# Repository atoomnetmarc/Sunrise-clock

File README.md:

# Status

**Experimental. Do not replicate.**

# Sunrise clock-hardware

Schematic and PCB files of the Sunrise clock. This sunrise clock tries to gently wake the user from its sleep using digital leds (SK6812) to simulate a sunrise and simultaneously playing soothing sounds through its crappy speaker using a I2S mono amplifier.\
1 display was not enough to view the time when the user has trouble dealing with dry eye syndrome so there are 3 displays capable of displaying a few characters each with a large font. Also, no touch screen so the user is able to change settings without looking using large-ish tactile buttons.

How the sunrise clock could look like:

My [Kicad library](https://github.com/atoomnetmarc/ATOOMNETKICAD) is used in this project.

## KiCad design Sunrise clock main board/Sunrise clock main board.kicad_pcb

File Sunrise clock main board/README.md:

# Status

**Experimental. Do not replicate.**

# Checklist V1.0 PCB

Worky (after workaround)?

:ballot_box_with_check: SD card auto disconnect when programming via USB\
:ballot_box_with_check: SD card, 1-bit SDIO\
:ballot_box_with_check: SD card, HSPI\
:ballot_box_with_check: RTC battery voltage follower opamp\
:ballot_box_with_check: 3.3V I2C\
:ballot_box_with_check: 5V I2C\
:ballot_box_with_check: INA219 current/power measuring\
:ballot_box_with_check: AT24C512C EEPROM\
:ballot_box_with_check: DS3231MZ mems RTC\
:ballot_box_with_check: BME280 sensor\
:ballot_box_with_check: MCP23017 I/O expander\
:ballot_box_with_check: LDR\
:ballot_box_with_check: LCD displays\
:ballot_box_with_check: Neopixel\
:ballot_box_with_check: Polyfuse F1\
:ballot_box_with_check: GPO2\
:ballot_box_with_check: I2S audio amplifier left channel (mono)\
:black_square_button: I2S audio amplifier right channel

# Errata

## V1.1

- Not build yet.

## V1.0

- VREF2 of U6 is incorrectly connected to +5V. It should be connected to EN. Workaround by disconnecting trace to VREF2 (pin7) and then connect EN (pin8) and VREF2 together.
- BME280 module A5 is a 5V one. Changed it for a 3.3V one. Workaround by disconnecting VCC from 5V and connect it to 3V.
- VIH of U8 74AHC125D on 5V too low for ESP32 output. Workaround by changing U8 from 74AHC125D to 74AHCT125D.
- INTA output voltage of MCP23017 exceeding input voltage of ESP32. Workaround by adding a 4K7/10K resistor divider.
- When powering the ESP32 by USB, the entire boards gets powered including the LED-strip which can potentially pull more than USB can provide. Workaround by moving D1 from parallel to ground and 5V to in series of 5V.
- External IO current measuring does not work with loads under 200mA and not great above that. Workaround by fitting a INA219 module between the 5V input of J1 and the rest of the board.

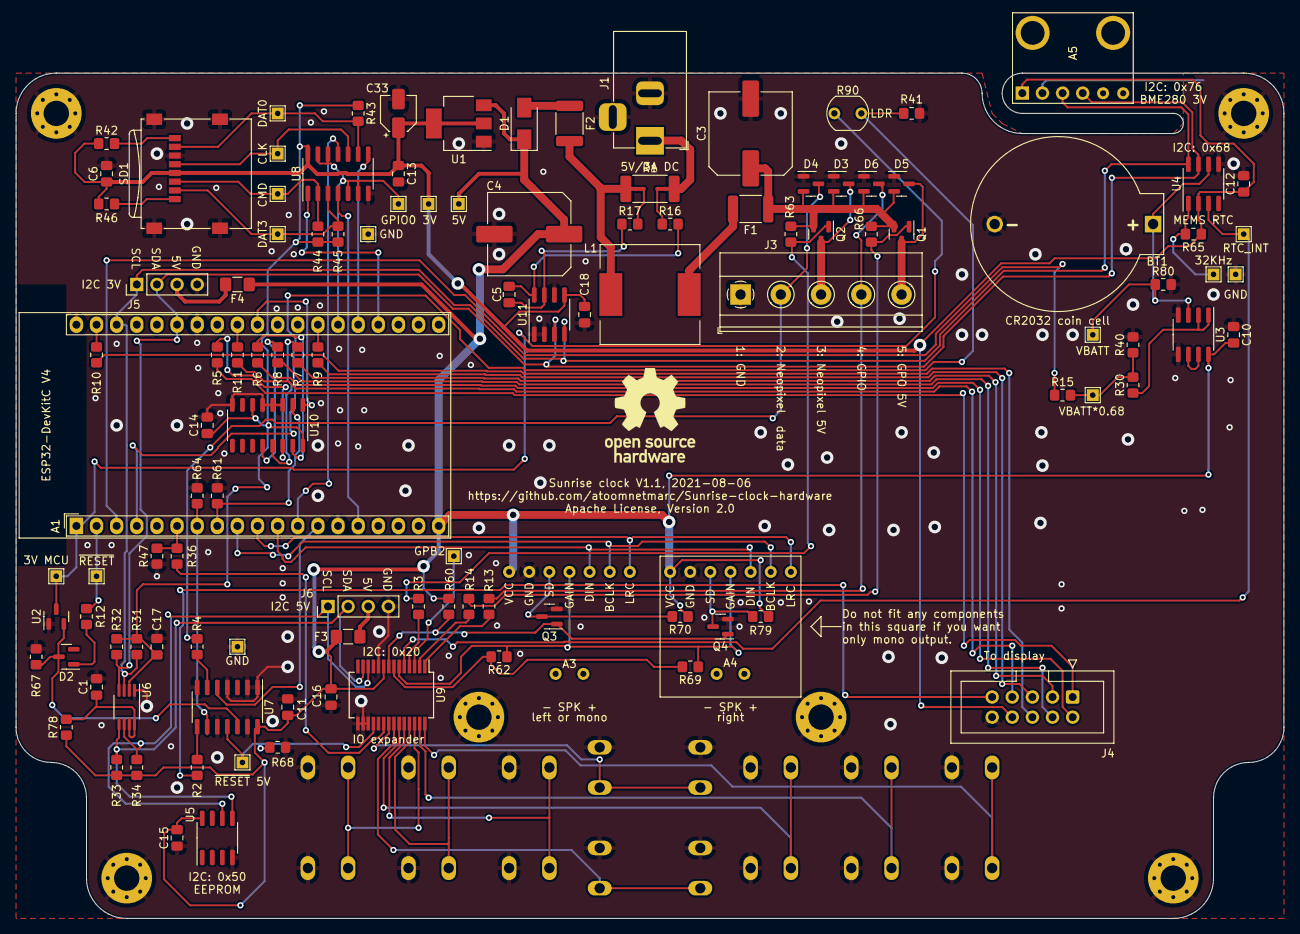
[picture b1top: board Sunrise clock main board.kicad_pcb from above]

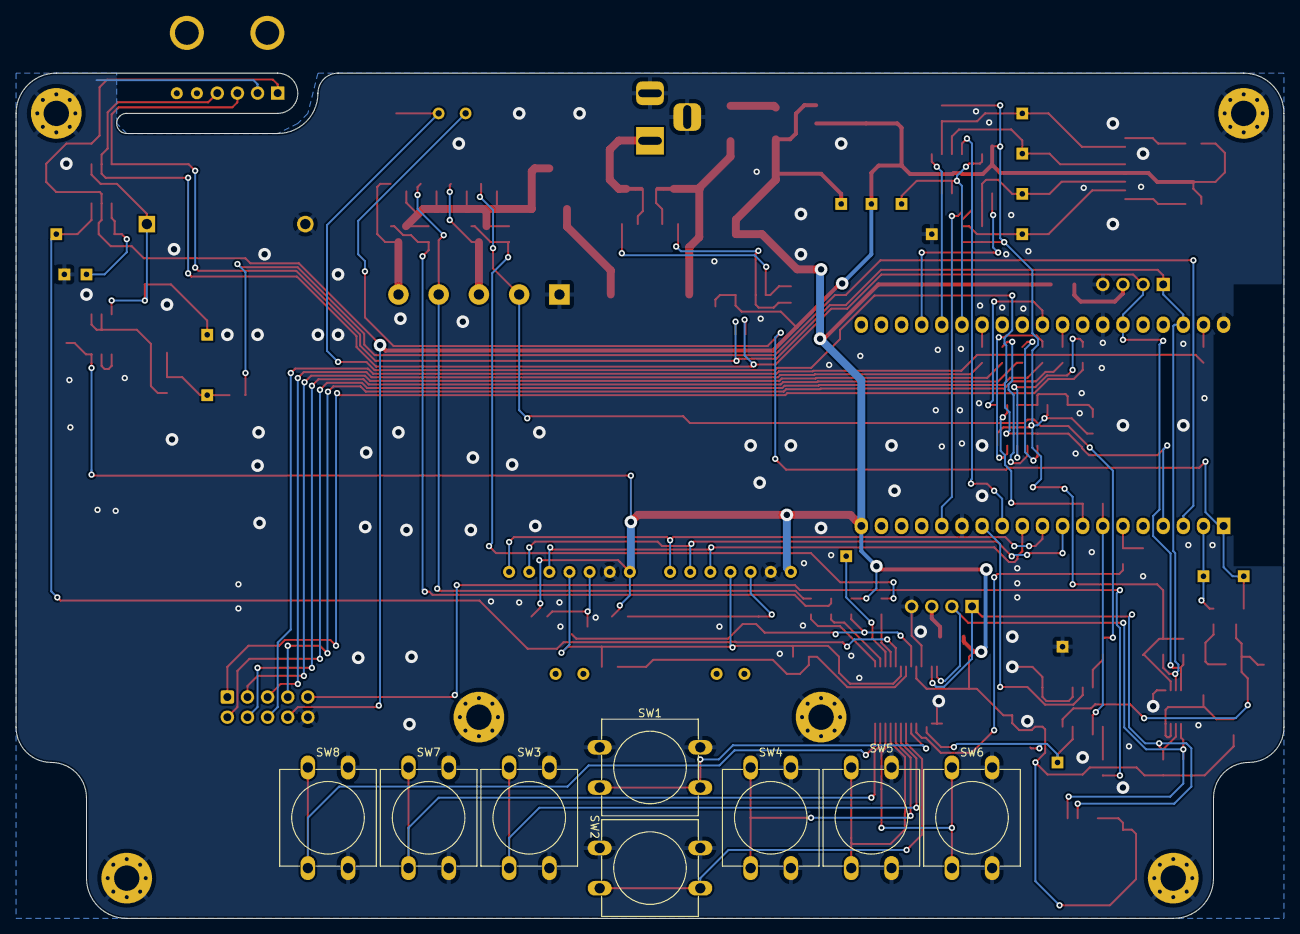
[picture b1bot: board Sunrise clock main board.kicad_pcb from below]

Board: 2 copper layers, 160.0 x 106.7 mm, 133 parts (8 on the bottom side), 92 nets.

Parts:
A1: ESP32-DevKitC
A3, A4: max98357
A5: BME280 module 3V; bme280_3V
BT1: CR2032; BatteryHolder-cr2032
C1: 100pF 16V X7R; C_0805_2012Metric_Pad1.18x1.45mm_HandSolder
C3, C4: 470uF/16V; C_Elec_10x10.2
C5: 1uF; C_0805_2012Metric_Pad1.18x1.45mm_HandSolder
C6: 10uF; C_0805_2012Metric_Pad1.18x1.45mm_HandSolder
C10, C11, C12, C13, C14, C15, C16, C17, C18: 100nF; C_0805_2012Metric_Pad1.18x1.45mm_HandSolder
C33: 33uF/6.3V; CP_Elec_4x5.4
D1: SS34; D_SMA
D2, D3, D4, D5, D6: BAV99; SOT-23
F1, F2: Polyfuse 1.5A >=6V; Fuse_1812_4532Metric_Pad1.30x3.40mm_HandSolder
F3, F4: Polyfuse 250mA >=6V; Fuse_1206_3216Metric_Pad1.42x1.75mm_HandSolder
H1, H2, H3, H4, H5, H6: MountingHole_Pad; MountingHole_3.2mm_M3_Pad_Via
J1: Barrel_Jack_Switch; BarrelJack_Horizontal
J3: Screw terminal/dnf; TerminalBlock_Phoenix_MKDS-1,5-5-5.08_1x05_P5.08mm_Horizont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
J4: Conn_02x05_Odd_Even; IDC-Header_2x05_P2.54mm_Vertical
J5, J6: Conn_01x04_Male; PinHeader_1x04_P2.54mm_Vertical
L1: 22uH 3A; L_12x12mm_H8mm
LOGO1: Logo_Open_Hardware_Large; OSHW-Logo_11.4x12mm_SilkScreen
NT1, NT2: Net-Tie_2; NetTie-2_SMD_Pad0.5mm
Q1, Q2: IRML2244; SOT-23
Q3, Q4: 2N7002; SOT-23
R1: 0R05; R_2512_6332Metric_Pad1.40x3.35mm_HandSolder
R2, R3, R4, R5, R6, R7, R8, R9, R10, R11, R12, R13, R14, R15: 100R; R_0805_2012Metric_Pad1.20x1.40mm_HandSolder
R16, R17: 10R; R_0805_2012Metric_Pad1.20x1.40mm_HandSolder
R30, R31, R32, R33, R34, R36: 4k7; R_0805_2012Metric_Pad1.20x1.40mm_HandSolder
R40, R41, R42, R43, R44, R45, R46, R47: 10k; R_0805_2012Metric_Pad1.20x1.40mm_HandSolder
R60, R61, R62, R63, R64, R65, R66, R67, R68, R69, R70: 100k; R_0805_2012Metric_Pad1.20x1.40mm_HandSolder
R78: 200k; R_0805_2012Metric_Pad1.20x1.40mm_HandSolder
R79: 560k; R_0805_2012Metric_Pad1.20x1.40mm_HandSolder
R80: 10M; R_0805_2012Metric_Pad1.20x1.40mm_HandSolder
R90: LDR GL5528; R_LDR_5.1x4.3mm_P3.4mm_Vertical
SD1: Micro_SD_Card; microSD_HC_Wuerth_693072010801
SW1, SW2, SW3, SW4, SW5, SW6, SW7, SW8: SW_Push; SW_PUSH-12mm
TP1, TP3, TP4, TP6, TP7, TP8, TP9, TP10, TP11, TP12, TP13, TP14, TP15, TP16, TP17, TP18, TP19, TP20: TestPoint; TestPoint_THTPad_1.5x1.5mm_Drill0.7mm
U1: NCP1117LPST33T3G; SOT-223-3_TabPin2
U2: MAX809S; SOT-23
U3: LM358DR; SOIC-8_3.9x4.9mm_P1.27mm
U4: DS3231MZ; SOIC-8_3.9x4.9mm_P1.27mm
U5: AT24C512C-SSHD; SOIC-8_3.9x4.9mm_P1.27mm
U6: PCA9306DCTR; MSOP-8_3x3mm_P0.65mm
U7: 74AHCT125D; SO-14_3.9x8.65mm_P1.27mm
U8: 74HC4066D; SO-14_3.9x8.65mm_P1.27mm
U9: MCP23017_SP; SSOP-28_5.3x10.2mm_P0.65mm
U10: 74HC138D; SO-16_3.9x9.9mm_P1.27mm
U11: INA219AxD; SOIC-8_3.9x4.9mm_P1.27mm

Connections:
3V_MCU: A1.1 (3V3_OUT), R90.1, TP6.1, U2.3 (VDD)
+3V3: A5.1 (VIN), C6.1, C12.1, C13.1, C14.1, C17.1, C18.1, C33.1, J4.8, R31.1, R32.1, R42.1, R43.1, R44.1, R45.1, R46.1, R65.1, SD1.4 (VDD), TP4.1, U1.2 (VO), U4.2 (VCC), U6.2 (VREF1), U8.14 (VDD), U10.6 (E3), U10.16 (VCC), U11.5 (VS)
+5V: A1.19 (5V_IN), A3.7 (VCC), A4.7 (VCC), C4.1, C10.1, C11.1, C15.1, C16.1, D1.1 (K), F3.2, F4.1, R33.1, R34.1, R60.2, R70.2, R78.1, R79.2, TP3.1, U1.3 (VI), U3.8 (V+), U5.8 (VCC), U7.14 (VCC), U9.9 (VDD)
+5VL: F2.2, L1.1, NT1.1, R1.1
+BATT: BT1.1 (+), R80.1, TP9.1, U3.3 (+), U4.6 (VBAT)
/Input/32KHz: R65.2, TP10.1, U4.1 (32KHZ)
/Output/GPO2_5V: D5.3 (K), J3.5, Q1.3 (D)
/Output/NEOPIXEL_5V: D3.3 (K), J3.3, Q2.3 (D)
/Output/NEOPIXEL_DOUT: D4.3 (K), J3.2, R4.1
/Power/VBATT*0.68: R15.2, R30.2, R40.1, TP8.1
/Storage/CLK: SD1.5 (CLK), TP15.1, U8.10
/Storage/CMD: R44.2, SD1.3 (CMD), TP14.1, U8.2
/Storage/DAT0: R43.2, SD1.7 (DAT0), TP16.1, U8.9
/Storage/DAT1: R42.2, SD1.8 (DAT1)
/Storage/DAT2: R46.2, SD1.1 (DAT2)
/Storage/DAT3: R45.2, SD1.2 (DAT3/CD), TP13.1, U8.3
EXP_INT: R36.1, U9.20 (INTA)
GND: A1.14 (GND), A1.32 (GND), A1.38 (GND), A3.6 (GND), A4.6 (GND), A5.2 (GND), BT1.2 (-), C1.2, C3.2, C4.2, C6.2, C10.2, C11.2, C12.2, C13.2, C14.2, C15.2, C16.2, C17.2, C18.2, C33.2, D3.1 (K), D4.1 (K), D5.1 (K), D6.1 (K), H1.1, H2.1, H3.1, H4.1, H5.1, H6.1, J1.2, J1.3, J3.1, J4.10, J5.4, J6.4, Q3.2 (S), Q4.2 (S), R40.2, R41.2, R47.1, R61.1, R64.2, R67.2, R68.2, R80.2, SD1.6 (VSS), SD1.9 (SHIELD), SW1.2, SW2.2, SW3.2, SW4.2, SW5.2, SW6.2, SW7.2, SW8.2, TP1.1, TP19.1, TP20.1, U1.1 (GND), U2.1 (GND), U3.4 (V-), U3.5 (+), U4.5 (GND), U5.4 (GND), U6.1 (GND), U7.1, U7.2, U7.4, U7.7 (GND), U7.10, U7.13, U8.7 (VSS), U9.10 (VSS), U9.15 (A0), U9.16 (A1), U9.17 (A2), U10.3 (A2), U10.4 (E1), U10.5 (E2), U10.8 (GND), U11.1 (A1), U11.2 (A0), U11.6 (GND)
GPA0: SW1.1, U9.21 (GPA0)
GPA1: SW2.1, U9.22 (GPA1)
GPA2: SW3.1, U9.23 (GPA2)
GPA3: SW4.1, U9.24 (GPA3)
GPA4: SW5.1, U9.25 (GPA4)
GPA5: SW6.1, U9.26 (GPA5)
GPA6: SW7.1, U9.27 (GPA6)
GPA7: SW8.1, U9.28 (GPA7)
GPIO0: A1.25 (BH/IO0), TP12.1, U8.5, U8.6, U8.12, U8.13
GPIO1: R13.2, U9.1 (GPB0)
GPIO5: A1.29 (SPI_CS0/BH/IO5), U10.1 (A0)
GPIO33: A1.8 (XTAL32K/IO33), R61.2, U10.2 (A1)
GPO2: R14.2, U9.2 (GPB1)
I2S_BCK: A1.9 (IO25/DAC1), A3.2 (BLCK), A4.2 (BLCK)
I2S_DATA: A1.11 (IO27), A3.3 (DIN), A4.3 (DIN)
I2S_GAIN0: A3.4 (GAIN), A4.4 (GAIN), R62.1, R69.1, U9.6 (GPB5)
I2S_GAIN1: R62.2, R69.2, U9.7 (GPB6)
I2S_SD: Q3.1 (G), Q4.1 (G), R60.1, U9.8 (GPB7)
I2S_WS: A1.10 (IO26/DAC2), A3.1 (LRC), A4.1 (LRC)
LCD1_~CE: J4.2, R6.1
LCD2_~CE: J4.3, R7.1
LCD3_~CE: J4.4, R8.1
LCD_CLK: J4.7, R11.1
LCD_DATA-~CMD: J4.5, R9.1
LCD_DIN: J4.6, R10.1
LCD_LED: A1.7 (XTAL32K/IO32), R64.1, U7.9
LCD_~RST: J4.1, R5.1
LDR: A1.4 (SENSOR_VN), R41.1, R90.2
NEOPIXEL_DATA: A1.13 (IO12/TDI/Bnc), U7.5
NEOPIXEL_~EN: R3.2, U9.4 (GPB3)
unnamed: A1.6 (IO35), R36.2, R47.2
unnamed: A1.26 (BL/IO4), R9.2
unnamed: A1.30 (SPI_CLK/IO18), R11.2
unnamed: A1.37 (SPI_MOSI/IO23), R10.2
unnamed: C1.1, R78.2, U6.7 (VREF2), U6.8 (EN)
unnamed: C3.1, D3.2 (A), D4.2 (A), D5.2 (A), D6.2 (A), F1.1, Q1.2 (S), Q2.2 (S), R63.1, R66.1
unnamed: C5.1, R16.1, U11.8 (IN+)
unnamed: C5.2, R17.1, U11.7 (IN-)
unnamed: D1.2 (A), F2.1
unnamed: D2.1 (K), R12.2
unnamed: D2.3 (K), R67.1, U2.2 (~RESET), U7.12
unnamed: D6.3 (K), J3.4, R13.1
unnamed: F1.2, L1.2
unnamed: F3.1, J6.3
unnamed: F4.2, J5.3
unnamed: J1.1, NT2.1, R1.2
unnamed: J4.9, R2.1
unnamed: Q1.1 (G), R14.1, R66.2
unnamed: Q2.1 (G), R3.1, R63.2
unnamed: R2.2, U7.8
unnamed: R4.2, U7.6
unnamed: R5.2, U10.14 (O1)
unnamed: R6.2, U10.15 (O0)
unnamed: R7.2, U10.13 (O2)
unnamed: R8.2, U10.12 (O3)
unnamed: R30.1, U3.1, U3.2 (-)
unnamed: TP18.1, U9.3 (GPB2)
unnamed: U3.6 (-), U3.7
RTC_INT: TP11.1, U4.3 (~INT/SQW), U9.5 (GPB4)
SCL_3V: A1.36 (IO22/SCL), A5.3 (SCL), J5.1, R31.2, U4.8 (SCL), U6.3 (SCL1), U11.4 (SCL)
SCL_5V: J6.1, R34.2, U5.6 (SCL), U6.6 (SCL2), U9.12 (SCK)
SDA_3V: A1.33 (IO21/SDA), A5.4 (SDA), J5.2, R32.2, U4.7 (SDA), U6.4 (SDA1), U11.3 (SDA)
SDA_5V: J6.2, R33.2, U5.5 (SDA), U6.5 (SDA2), U9.13 (SDA)
SD_CLK_SCK: A1.12 (IO14/TMS), U8.11
SD_CMD_MOSI: A1.23 (IO15/TDO/BH), U8.1
SD_D0_MISO: A1.24 (BL/IO2), U8.8
SD_SPI_SS: A1.15 (IO13/TCK), U8.4
VBAT_DIV: A1.3 (SENSOR_VP), R15.1
VIN+: NT2.2, R16.2
VIN-: NT1.2, R17.2
~RESET_5V: R68.1, TP17.1, U7.11, U9.18 (~RESET)
~RESET: A1.2 (EN), R12.1, TP7.1
~SDL: A3.5 (SD), Q3.3 (D), R70.1
~SDR: A4.5 (SD), Q4.3 (D), R79.1

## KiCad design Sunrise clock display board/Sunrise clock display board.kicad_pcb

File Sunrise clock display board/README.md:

# Status

**Experimental. Do not replicate.**

# Checklist V1.0 PCB

Worky (after bodge fix)?

:ballot_box_with_check: SD card auto disconnect when programming via USB
:ballot_box_with_check: SD card, 1-bit SDIO
:ballot_box_with_check: SD card, HSPI
:ballot_box_with_check: RTC battery voltage follower opamp
:ballot_box_with_check: LED-strip current measuring opamp
:black_square_button: 3.3V I2C
:black_square_button: 5V I2C
:black_square_button: AT24C512C EEPROM
:black_square_button: DS3231MZ mems RTC
:black_square_button: BME280 sensor
:black_square_button: MCP23017 I/O expander
:black_square_button: LDR
:black_square_button: LCD displays
:black_square_button: Neopixel
:black_square_button: Polyfuse F1
:black_square_button: GPO2
:black_square_button: I2S audio amplifier left channel (mono)
:black_square_button: I2S audio amplifier right channel

# Errata

## V1.1

- Not build yet.

## V1.0

- VREF2 of U6 is incorrectly connected to +5V. It should be connected to EN. Workaround by disconnecting trace to VREF2 (pin7) and then connect EN (pin8) and VREF2 together.
- BME280 module A5 is a 5V one. Changed it for a 3.3V one. Workaround by disconnecting VCC from 5V and connect it to 3V.
- VIH of U8 74AHC125D on 5V too low for ESP32 output. Workaround by changing U8 from 74AHC125D to 74AHCT125D.

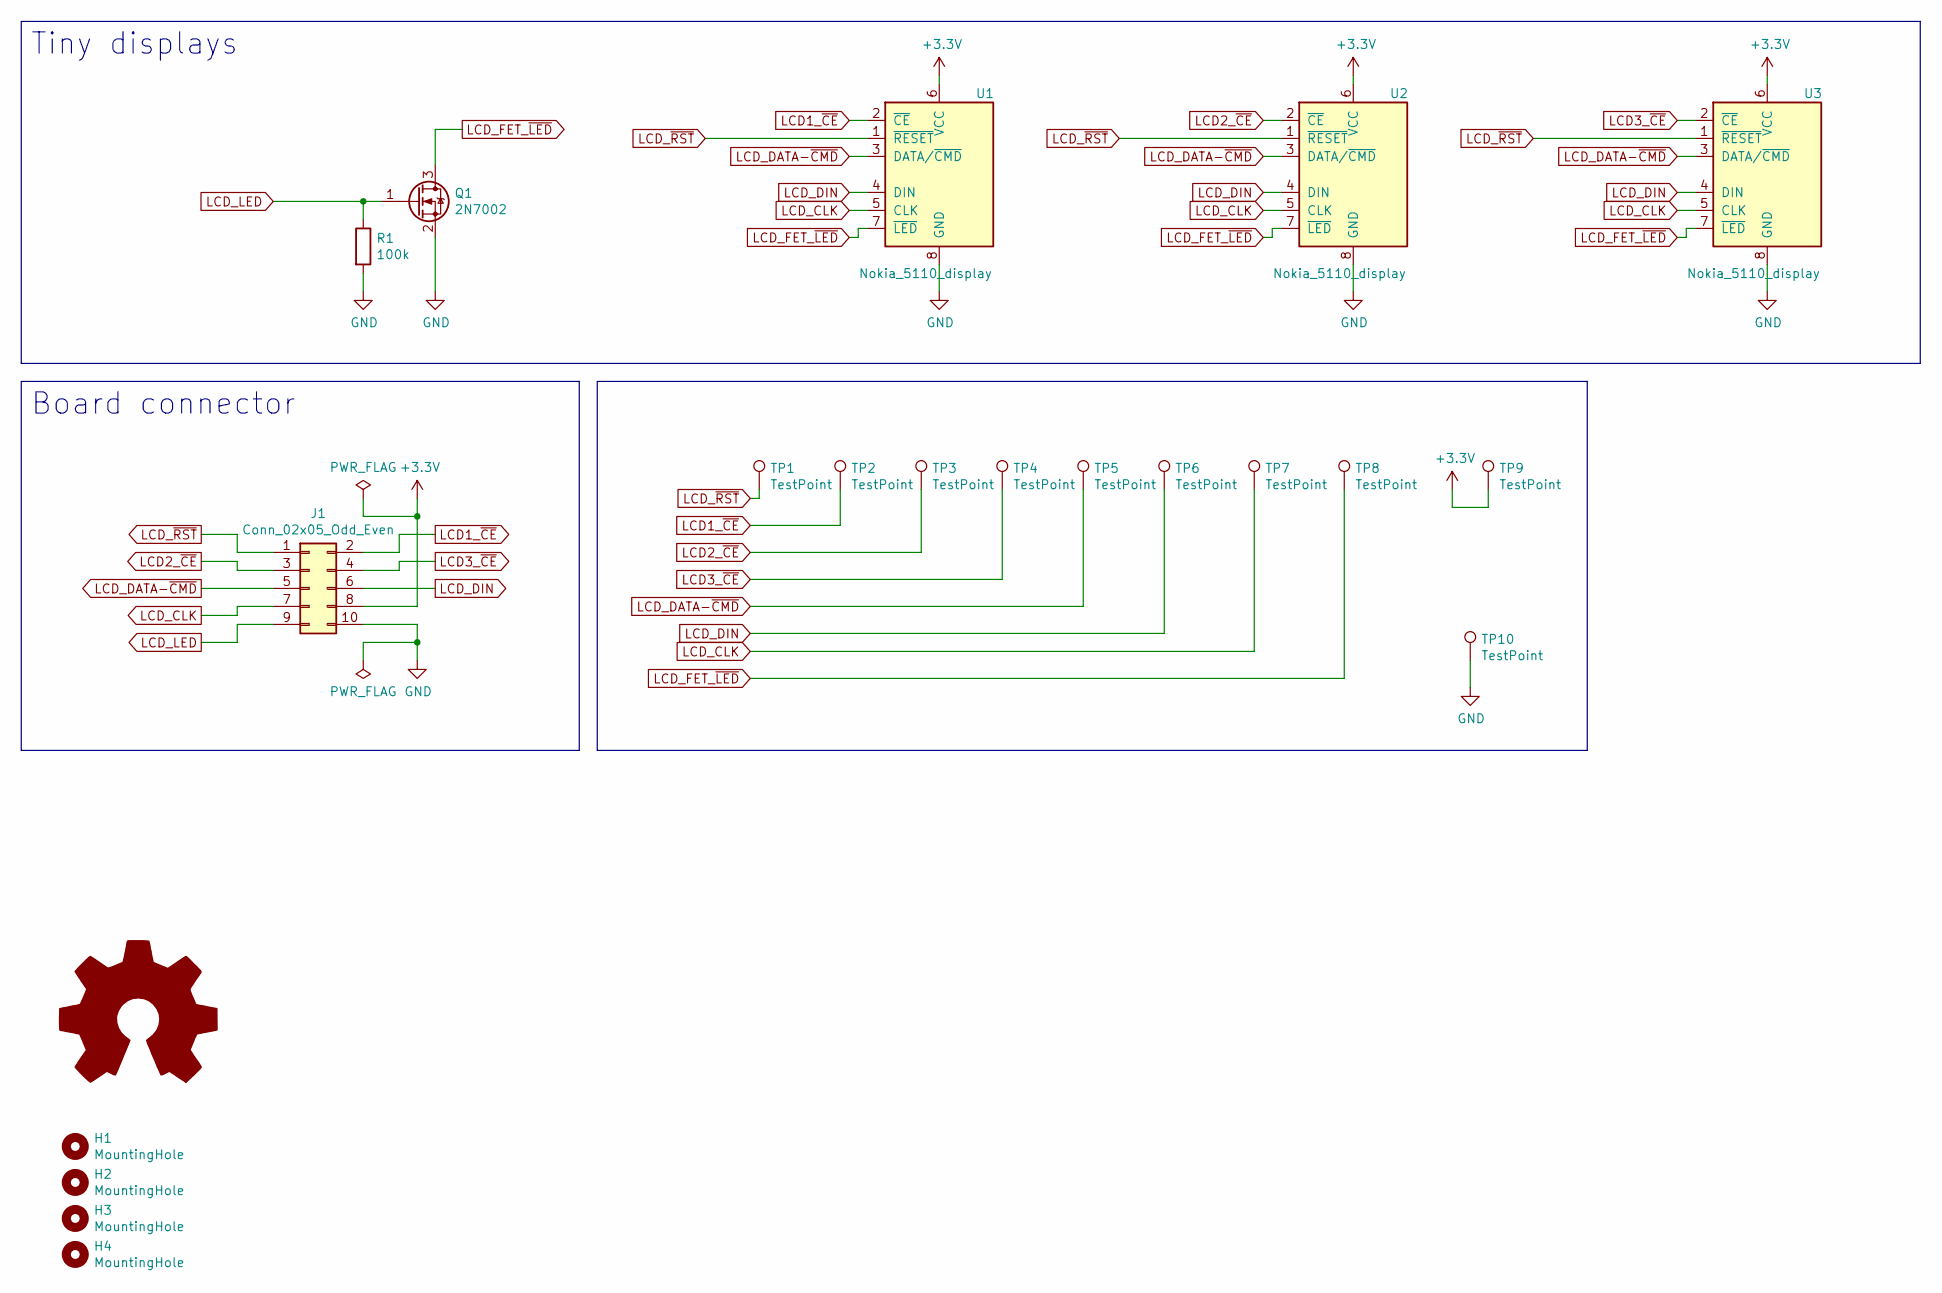
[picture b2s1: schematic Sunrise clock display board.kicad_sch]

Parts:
H1, H2, H3, H4: MountingHole; MountingHole_3.2mm_M3_Oval_5mm
J1: Conn_02x05_Odd_Even; IDC-Header_2x05_P2.54mm_Vertical
LOGO1: Logo_Open_Hardware_Large; OSHW-Logo_19x20mm_SilkScreen
Q1: 2N7002; SOT-23
R1: 100k; R_0805_2012Metric_Pad1.20x1.40mm_HandSolder
TP1, TP2, TP3, TP4, TP5, TP6, TP7, TP8, TP9, TP10: TestPoint; TestPoint_THTPad_1.5x1.5mm_Drill0.7mm
U1, U2, U3: Nokia_5110_display; Nokia_5110_display_module

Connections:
+3V3: J1.8, TP9.1, U1.6 (VCC), U2.6 (VCC), U3.6 (VCC)
GND: J1.10, Q1.2 (S), R1.2, TP10.1, U1.8 (GND), U2.8 (GND), U3.8 (GND)
LCD1_~CE: J1.2, TP2.1, U1.2 (~CE)
LCD2_~CE: J1.3, TP3.1, U2.2 (~CE)
LCD3_~CE: J1.4, TP4.1, U3.2 (~CE)
LCD_CLK: J1.7, TP7.1, U1.5 (CLK), U2.5 (CLK), U3.5 (CLK)
LCD_DATA-~CMD: J1.5, TP5.1, U1.3 (DATA/~CMD), U2.3 (DATA/~CMD), U3.3 (DATA/~CMD)
LCD_DIN: J1.6, TP6.1, U1.4 (DIN), U2.4 (DIN), U3.4 (DIN)
LCD_FET_~LED: Q1.3 (D), TP8.1, U1.7 (~LED), U2.7 (~LED), U3.7 (~LED)
LCD_LED: J1.9, Q1.1 (G), R1.1
LCD_~RST: J1.1, TP1.1, U1.1 (~RESET), U2.1 (~RESET), U3.1 (~RESET)

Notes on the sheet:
Board connector
Tiny displays

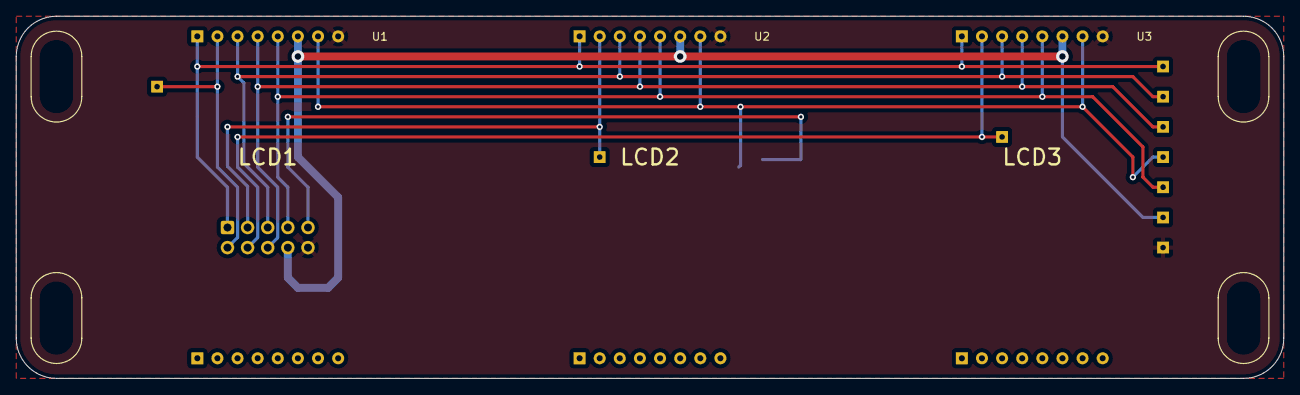
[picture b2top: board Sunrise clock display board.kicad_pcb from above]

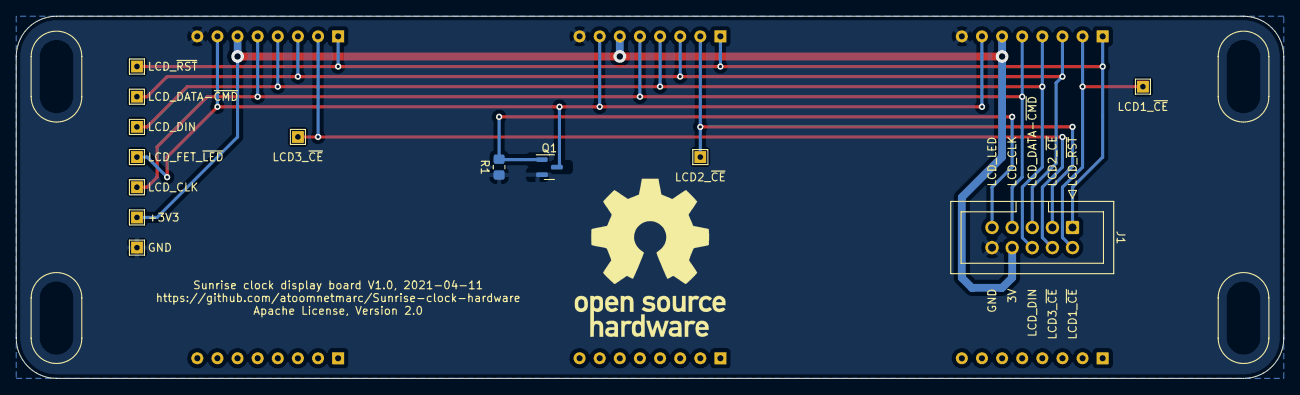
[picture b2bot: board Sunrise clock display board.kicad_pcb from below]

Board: 2 copper layers, 160.0 x 45.7 mm, 21 parts (14 on the bottom side), 11 nets.

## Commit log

2021-04-09 Initial commit.
2021-04-09 More better English.
2021-04-09 Tweaks
2021-04-10 Now in stereo if you want.
2021-04-11 Added gerbers and bom.
2021-04-24 updated lcd footprint
2021-05-02 Start of V1.1
2021-05-03 changed BME280 module to a 3v one
2021-05-03 Started with checklist.
2021-05-03 More testing.
2021-05-03 Tweak formatting.
2021-08-06 Changed INA219AxDCN to INA219AxD
2022-02-07 Update to Kicad 6.

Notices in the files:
README.md:
License: Apache 2.0
Sunrise clock display board/Sunrise clock display board.kicad_pcb:
Apache License, Version 2.0
